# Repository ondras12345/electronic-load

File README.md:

# Electronic load
This repository contains hardware designs and firmware for my electronic load.

## Hardware

This project is based on an analog electronic load PCB from Aliexpress:
XHDZ-FZ-2g.
Originally, I just put it in a box and used it as-is with a 10-turn
potentiometer. However, then the pot failed, and I decided to upgrade it with
digital control. The control loop is still analog utilising the original
circuitry, but the reference signal is generated by a microcontroller instead
of the potentiometer.

My `electronic-load-controller` PCB contains an ATmega8 microcontroller,
a PWM DAC to generate the reference voltage, UART optoisolators for remote
control, and circuitry for measuring the load voltage and current.
It connects to the analog PCB via the original connectors with just one wire
needing to be soldered to a non-standard pad on the board.

The user interface consists of an SSD1306 OLED display and a rotary encoder.

Space for improvement: I didn't spend much time designing the user interface
and as a result, I had to use a small font that is hard to read from a
distance.

## Software
The firmware on the ATmega microcontroller performs several functions.
It measures the voltage across the load, the load current, calculates the
power loss and implements over-power protection, monitors the heatsink
temperature and controls the cooling fan.
It uses the DAC to generate the current setpoint signal for the analog board
based on the value set by the user via the rotary encoder,
and it implements a SCPI interface on the serial port for remote control
capability.

### SCPI commands
A text-based remote control interface is available on the serial port (9600
baud, 8N1).

The following table explains the individual command (`v` is a placeholder for
an integer argument).

| command       | description                                                   |
|:-------------:|:--------------------------------------------------------------|
| `ISET v`      | Set load current. E.g. `ISET 1000` sets the current to 1A.    |
| `ISET?`       | Get load current setpoint value in mA.                        |
| `IGAIN v`     | Settings: set conversion coefficient for current measurement. |
| `IGAIN?`      | Settings: get `IGAIN` value.                                  |
| `VGAIN v`     | Settings: set conversion coefficient for voltage measurement. |
| `VGAIN?`      | Settings: get `VGAIN` value.                                  |
| `SPGAIN v`    | Settings: set conversion coefficient for current setpoint.    |
| `SPGAIN?`     | Settings: get `SPGAIN` value.                                 |
| `SPOFF v`     | Settings: set conversion offset for current setpoint.         |
| `SPOFF?`      | Settings: get `SPOFF` value.                                  |
| `DUTY?`       | Get PWM DAC duty cycle value. Useful for debugging.           |
| `I?`          | Get measured current in A.                                    |
| `V?`          | Get measured voltage in V.                                    |
| `P?`          | Get measured power in W.                                      |
| `TEMP?`       | Get heatsink temperature in degrees C.                        |
| `*BOOTLOADER` | Jump to bootloader to allow updating firmware.                |
| `*SAV`        | Save settings to EEPROM.                                      |
| `*RST`        | Reset the microcontroller.                                    |

### Calibration
Calibration is performed using SCPI commands on the serial interface.
The goal is to make the load current and voltage readings accurate
and to make the current setpoint match the actual load current.

TODO document calibration procedure.

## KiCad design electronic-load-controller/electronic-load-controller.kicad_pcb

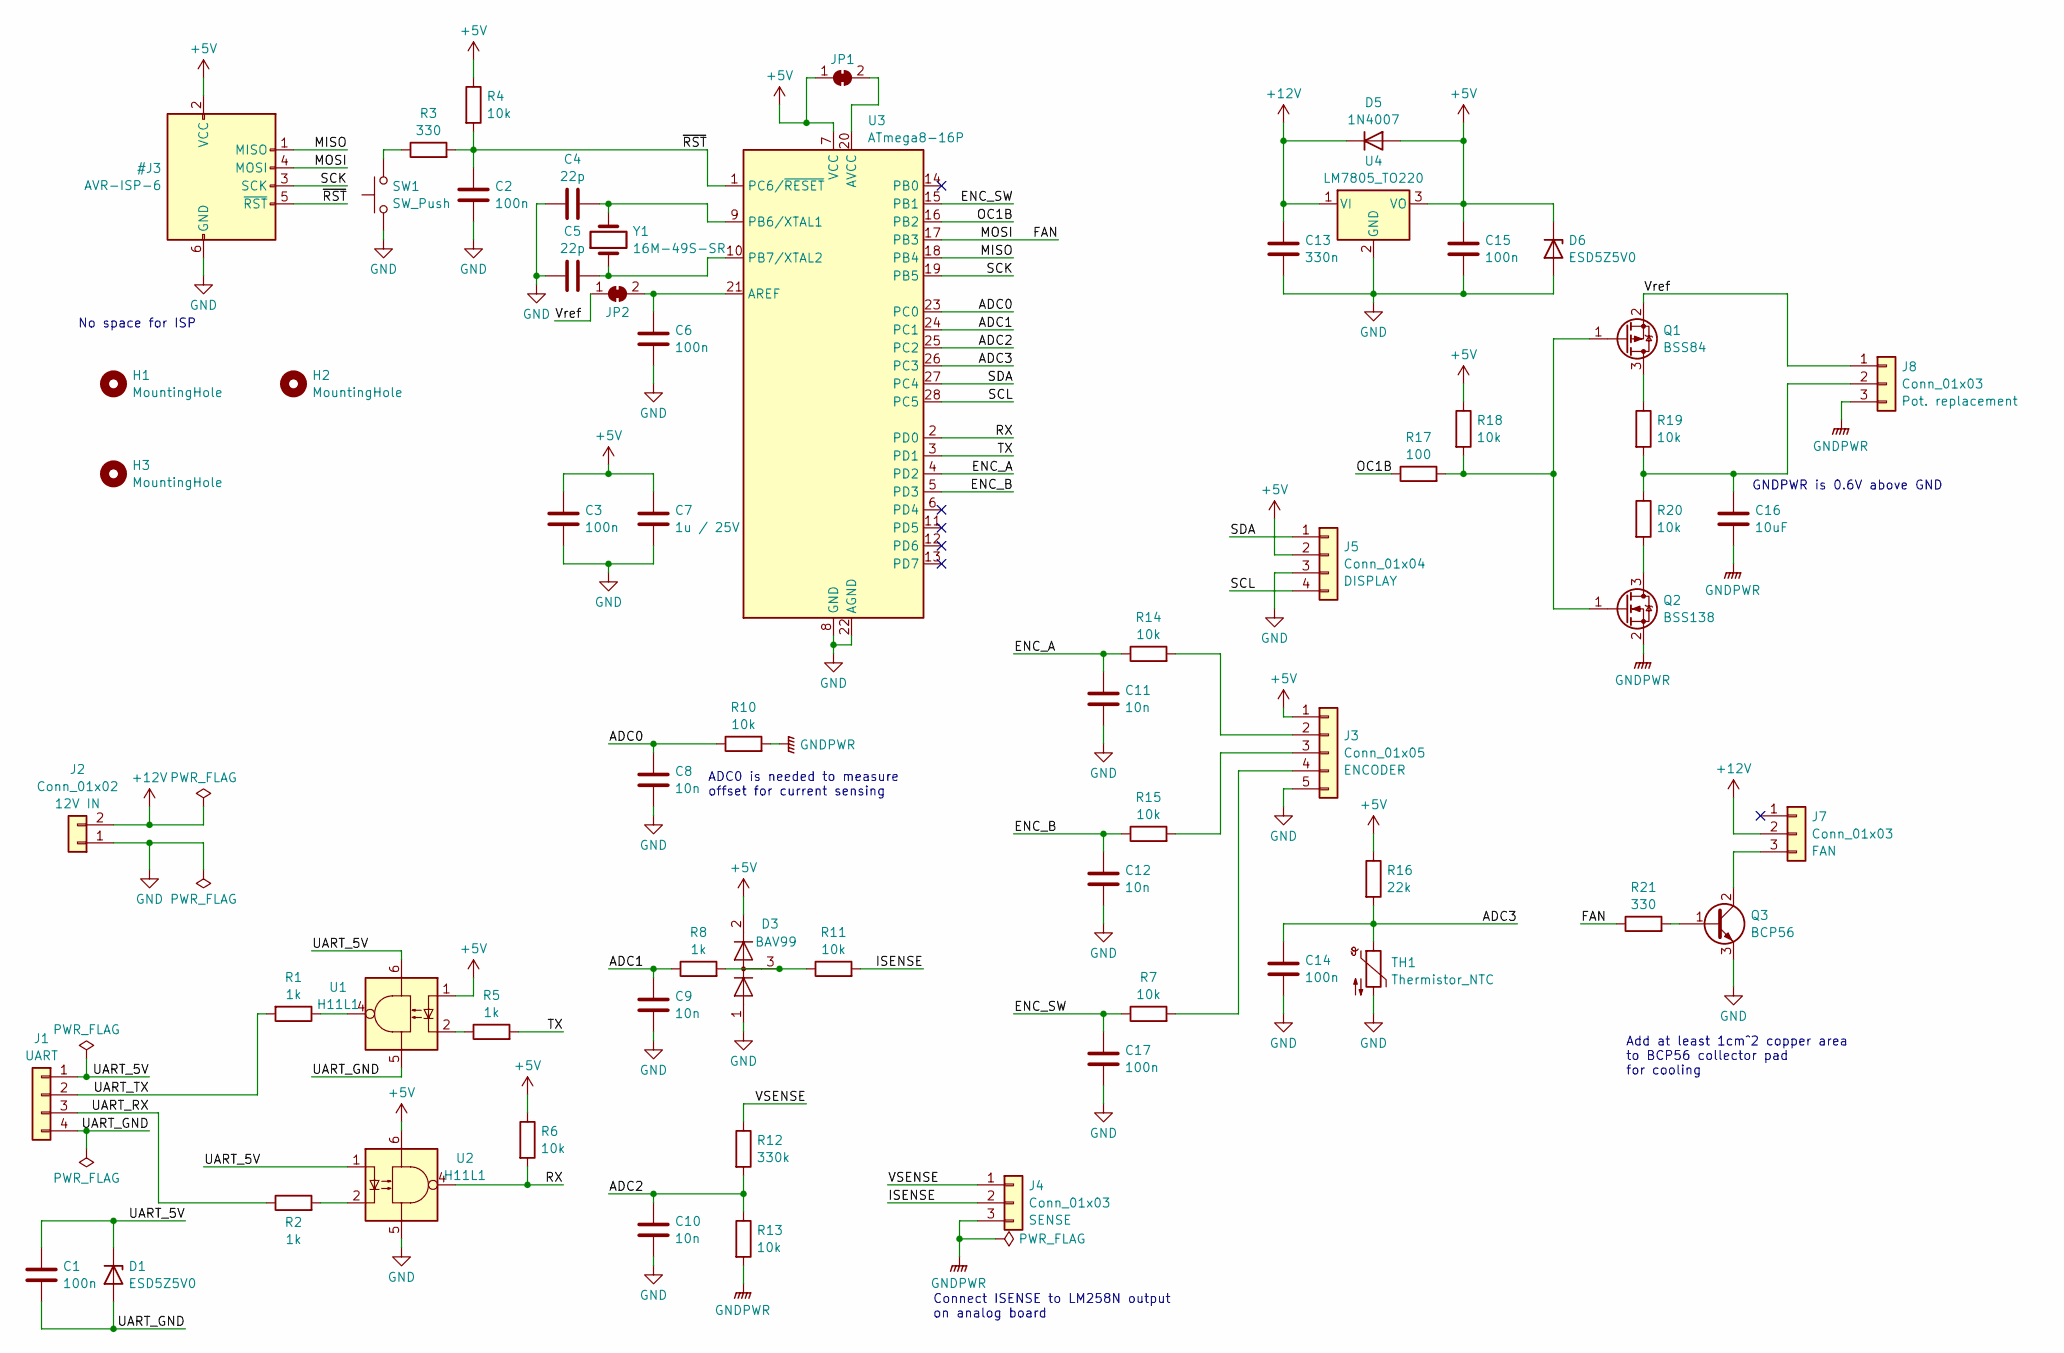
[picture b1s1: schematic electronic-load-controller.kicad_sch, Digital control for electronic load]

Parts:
C1, C2, C3, C6, C14, C15, C17: 100n; C_1206_3216Metric_Pad1.33x1.80mm_HandSolder
C4, C5: 22p; C_1206_3216Metric_Pad1.33x1.80mm_HandSolder
C7: 1u / 25V; C_1206_3216Metric_Pad1.33x1.80mm_HandSolder
C8, C9, C10, C11, C12: 10n; C_1206_3216Metric_Pad1.33x1.80mm_HandSolder
C13: 330n; C_1206_3216Metric_Pad1.33x1.80mm_HandSolder
C16: 10uF; C_1206_3216Metric_Pad1.33x1.80mm_HandSolder
D1, D6: ESD5Z5V0; D_SOD-523
D3: BAV99; SOT-23
D5: 1N4007; D_SMA_Handsoldering
H1, H2, H3: MountingHole; MountingHole_3.2mm_M3
J1, J5: Conn_01x04; Molex_KK-254_AE-6410-04A_1x04_P2.54mm_Vertical
J2: Conn_01x02; Molex_KK-254_AE-6410-02A_1x02_P2.54mm_Vertical
J3: Conn_01x05; Molex_KK-254_AE-6410-05A_1x05_P2.54mm_Vertical
J4, J7, J8: Conn_01x03; Molex_KK-254_AE-6410-03A_1x03_P2.54mm_Vertical
JP1, JP2: SolderJumper_2_Bridged; R_1206_3216Metric_Pad1.30x1.75mm_HandSolder
Q1: BSS84; SOT-23
Q2: BSS138; SOT-23
Q3: BCP56; SOT-223-3_TabPin2
R1, R2, R5, R8: 1k; R_1206_3216Metric_Pad1.30x1.75mm_HandSolder
R3, R21: 330; R_1206_3216Metric_Pad1.30x1.75mm_HandSolder
R4, R6, R7, R10, R11, R13, R14, R15, R18, R19, R20: 10k; R_1206_3216Metric_Pad1.30x1.75mm_HandSolder
R12: 330k; R_1206_3216Metric_Pad1.30x1.75mm_HandSolder
R16: 22k; R_1206_3216Metric_Pad1.30x1.75mm_HandSolder
R17: 100; R_1206_3216Metric_Pad1.30x1.75mm_HandSolder
SW1: SW_Push; SW_PUSH_6mm_H4.3mm
TH1: Thermistor_NTC; Molex_KK-254_AE-6410-02A_1x02_P2.54mm_Vertical
U1, U2: H11L1; DIP-6_W7.62mm_LongPads
U3: ATmega8-16P; DIP-28_W7.62mm
U4: LM7805_TO220; TO-220-3_Vertical
Y1: 16M-49S-SR; Crystal_HC49-U_Vertical

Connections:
+12V: C13.1, D5.1 (K), J2.2, J7.2, U4.1 (VI)
/ADC0: C8.1, R10.1, U3.23 (PC0)
/ADC1: C9.1, R8.1, U3.24 (PC1)
/ADC2: C10.1, R12.2, R13.1, U3.25 (PC2)
/ADC3: C14.1, R16.2, TH1.1, U3.26 (PC3)
/ENC_A: C11.1, R14.1, U3.4 (PD2)
/ENC_B: C12.1, R15.1, U3.5 (PD3)
/ENC_SW: C17.1, R7.1, U3.15 (PB1)
/ISENSE: J4.2, R11.2
/OC1B: R17.1, U3.16 (PB2)
/RX: R6.2, U2.4, U3.2 (PD0)
/SCL: J5.4, U3.28 (PC5)
/SDA: J5.1, U3.27 (PC4)
/TX: R5.2, U3.3 (PD1)
/UART_5V: C1.1, D1.1 (K), J1.1, U1.6, U2.1
/UART_GND: C1.2, D1.2 (A), J1.4, U1.5
/UART_RX: J1.3, R2.1
/UART_TX: J1.2, R1.2
/VSENSE: J4.1, R12.1
/Vref: J8.1, JP2.1 (A), Q1.2 (S)
GNDPWR: C16.2, J4.3, J8.3, Q2.2 (S), R10.2, R13.2
unnamed: D3.3 (K), R8.2, R11.1
unnamed: J3.2, R14.2
unnamed: J3.3, R15.2
unnamed: J3.4, R7.2
unnamed: J7.3, Q3.2 (C), Q3.4 (C)
unnamed: C16.1, J8.2, R19.2, R20.1
unnamed: JP1.2 (B), U3.20 (AVCC)
unnamed: C6.1, JP2.2 (B), U3.21 (AREF)
unnamed: Q1.3 (D), R19.1
unnamed: Q1.1 (G), Q2.1 (G), R17.2, R18.2
unnamed: Q2.3 (D), R20.2
unnamed: Q3.1 (B), R21.2
unnamed: R1.1, U1.4
unnamed: R2.2, U2.2
unnamed: R3.1, SW1.2
unnamed: R5.1, U1.2
unnamed: C4.2, U3.9 (PB6/XTAL1), Y1.2
unnamed: C5.2, U3.10 (PB7/XTAL2), Y1.1

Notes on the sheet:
Connect ISENSE to LM258N output on analog board
Add at least 1cm^2 copper area to BCP56 collector pad for cooling
No space for ISP
ADC0 is needed to measure offset for current sensing
GNDPWR is 0.6V above GND

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
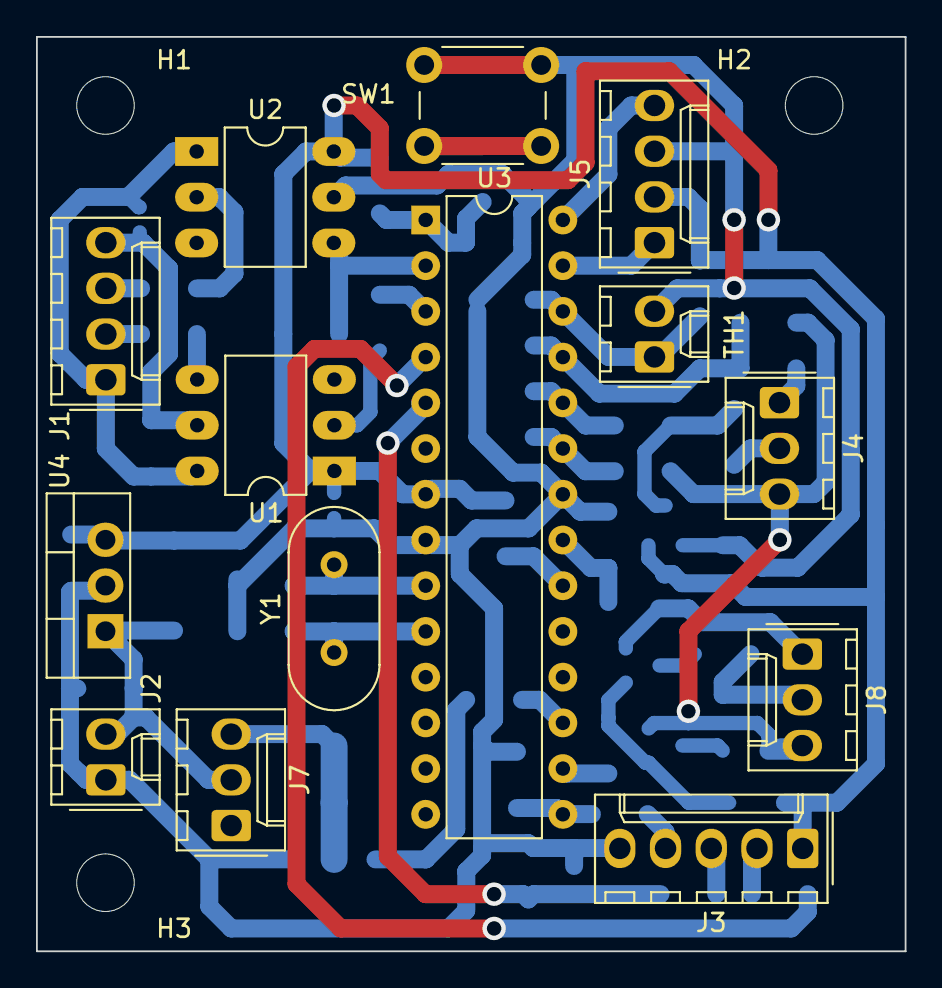
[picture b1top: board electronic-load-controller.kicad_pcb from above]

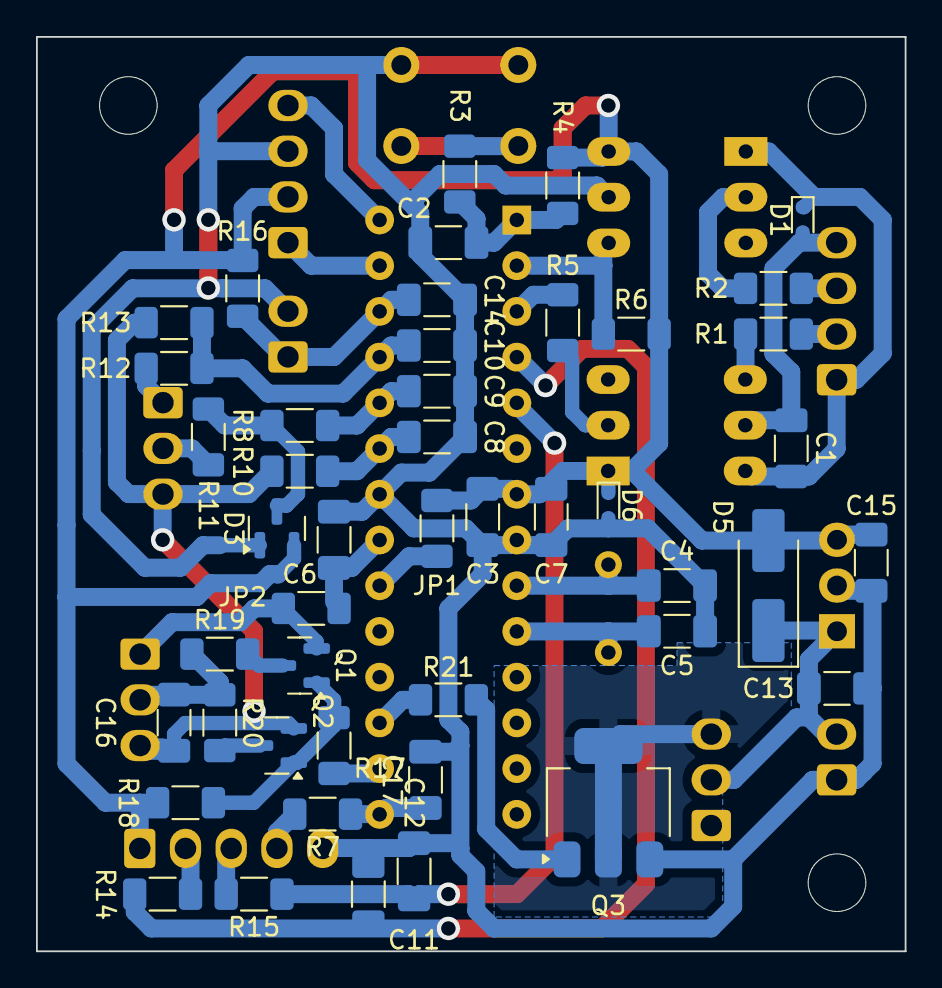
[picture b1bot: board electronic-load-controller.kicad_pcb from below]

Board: 2 copper layers, 48.3 x 50.8 mm, 63 parts (46 on the bottom side), 43 nets.

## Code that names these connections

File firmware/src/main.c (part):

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#include "serial_hash.h"

/*
PB1 .. ENC_SW
PB2 .. OC1B
PB3 .. FAN
PC0 .. ADC0 .. GNDPWR
PC1 .. ADC1 .. ISENSE
PC2 .. ADC2 .. VSENSE
PC3 .. ADC3 .. temperature
PC4 .. SDA
PC5 .. SCL

PD0 .. RX
PD1 .. TX
PD2 .. ENC_A
PD3 .. ENC_B
*/

#define PIN_ENCODER_SW  B, 1, 1 // PB1
#define PIN_PWM         B, 2, 2  // PB2
#define PIN_FAN         B, 3, 3  // PB3
#define PIN_ENCODER_AB  D, 3, 2  // PD3, PD2

// debounce times in ms
#define DEBOUNCE_ENCODER_SW 100U
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        case 56794:  // "*BOOTLOADER"
        {
            OCR1B = 0;  // duty
            gpio_set(PIN_FAN);

            _delay_ms(200);

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int main(void)
{
    gpio_conf(PIN_PWM, OUTPUT, 1);  // start with 0 current
    gpio_conf(PIN_FAN, OUTPUT, 1);  // start with fan on
    // inputs - nopullup is default
    //gpio_conf(PIN_ENCODER_AB, INPUT, NOPULLUP);
    //gpio_conf(PIN_ENCODER_SW, INPUT, NOPULLUP);
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        uint16_t fan_thres = fan ? TEMPERATURE_LOW : TEMPERATURE_HIGH;
        // if NTC is disconnected, it might report low temperature (or 0 on error)
        fan = (temperature_C10 > fan_thres || temperature_C10 < 10);
        if (fan) gpio_set(PIN_FAN);
        else gpio_clr(PIN_FAN);

        if (ADC_complete)
        {
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
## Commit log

2024-07-06 Add project files
2024-07-06 Increase I2C clock frequency
2024-07-06 Calculate duty from setpoint
2024-07-06 Handle encoder
2024-07-06 Remove SCPI, .text does not fit in flash
2024-07-06 Reduce debounce integrator width
2024-07-06 Implement UART interface
2024-07-06 Configure bootloader
2024-07-06 Use WDT, add command to jump to bootloader
2024-07-06 Save settings to EEPROM
2024-07-06 Add reset command
2024-07-06 Enable WDT before communicating with oled
2024-07-07 Add command to query duty
2024-07-07 Show cursor position on display
2024-07-07 Fix serial parsing
2024-07-07 Fix incorrect use of serial_puts_P
2024-07-07 Flash bootloader
2024-07-07 Testing
2024-07-08 Reduce I2C frequency to prevent display problems
2024-07-08 Fix encoder interrupts not enabled
2024-07-08 Only write encoder_pulses in ATOMIC_BLOCK
2024-07-08 Fix upload via bootloader
2024-07-08 Refresh display more often
2024-07-08 Fix encoder ignoring first step
2024-07-08 Remove setting defaults
2024-07-10 Reduce ADC sampling frequency
2024-07-10 Reduce width of millis_t to save flash space
2024-07-10 Display power
2024-07-10 Allow querying power via UART
2024-07-10 Refactor serial_parser to save FLASH space
    before:
    RAM: [== ] 24.8% (used 254 bytes from 1024 bytes)
    Flash: [==========] 99.4% (used 7632 bytes from 7680 bytes)
    after:
    RAM: [== ] 24.8% (used 254 bytes from 1024 bytes)
    Flash: [==========] 96.8% (used 7432 bytes from 7680 bytes)
2024-07-10 Remove useless UPTIME? command
    millis_t can only count up to 65 seconds
2024-07-10 Disable load by press + turn left
2024-07-12 Add lowpass filter to ADC
2024-07-13 Fix NTC temperature measurement
2024-07-13 Refactor display code
    before:
    RAM: [=== ] 26.4% (used 270 bytes from 1024 bytes)
    Flash: [==========] 98.2% (used 7540 bytes from 7680 bytes)
    after:
    RAM: [=== ] 26.4% (used 270 bytes from 1024 bytes)
    Flash: [==========] 97.9% (used 7518 bytes from 7680 bytes)
2024-07-13 Increase I2C clock speed
2024-07-14 Start at digit 2
2024-07-14 Update display one line at a time
    (All following builds were done with experimental power limit patch)
    before:
    RAM: [=== ] 26.5% (used 271 bytes from 1024 bytes)
    Flash: [==========] 98.4% (used 7556 bytes from 7680 bytes)
    after (all at once):
    RAM: [=== ] 26.6% (used 272 bytes from 1024 bytes)
2024-07-24 Calibrate current setpoint
    Refactoring was needed to fit in FLASH
2024-08-12 Limit power
2024-08-12 Add display bracket design
2024-08-12 Add NTC test
    Seems like I forgot to commit this file earlier.
2025-03-14 Add README.md
2025-03-14 Add KiCAD PDF outputs
2025-03-14 Rename outdated front panel design
2025-03-14 Add pictures to README
2025-03-14 Add LICENSE
2025-03-14 Add .gitignore
2025-03-14 Improve SCPI command list in README
